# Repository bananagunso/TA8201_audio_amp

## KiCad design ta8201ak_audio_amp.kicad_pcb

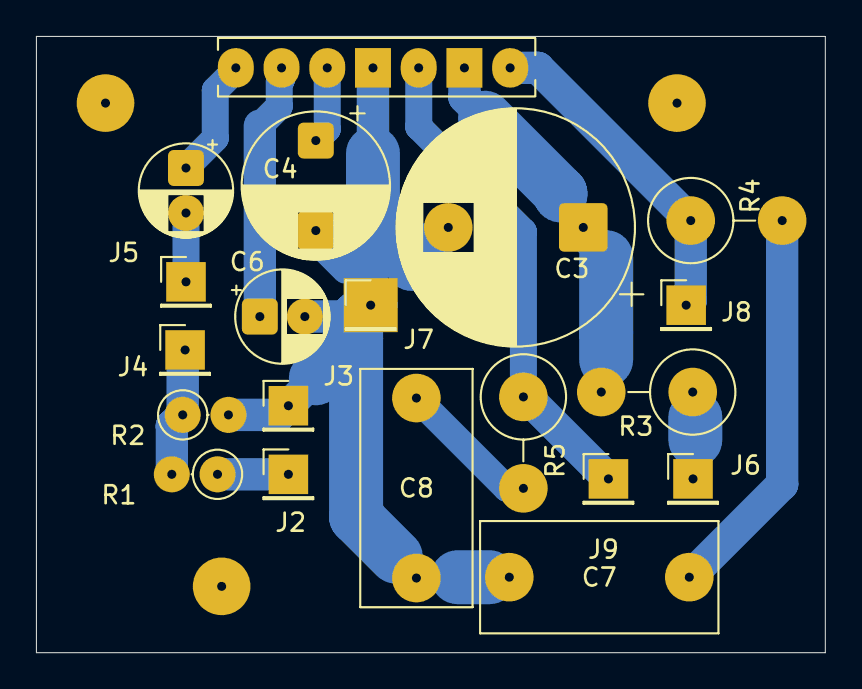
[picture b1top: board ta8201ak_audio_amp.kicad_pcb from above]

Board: 2 copper layers, 43.8 x 34.2 mm, 23 parts (0 on the bottom side), 13 nets.

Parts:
C3: 1000uF; CP_Radial_D13.0mm_P7.50mm
C4: 220u; CP_Radial_D8.0mm_P5.00mm
C5: 4.7u; CP_Radial_D5.0mm_P2.50mm
C6: 47u; CP_Radial_D5.0mm_P2.50mm
C7, C8: 0.15u; C_Rect_L13.0mm_W6.0mm_P10.00mm_FKS3_FKP3_MKS4
H1, H2, H3: MountingHole; MountingHole_3.2mm_M3
J2: IN; PinHeader_1x01_P2.54mm_Vertical
J3: GND; PinHeader_1x01_P2.54mm_Vertical
J4: RV1_3; PinHeader_1x01_P2.54mm_Vertical
J5: RV1_2; PinHeader_1x01_P2.54mm_Vertical
J6: Vcc; PinHeader_1x01_P2.54mm_Vertical
J7: Gnd; PinHeader_1x01_P2.54mm_Vertical
J8: Out1; PinHeader_1x01_P2.54mm_Vertical
J9: Out2; PinHeader_1x01_P2.54mm_Vertical
R1: 200k; R_Axial_DIN0207_L6.3mm_D2.5mm_P2.54mm_Vertical
R2: 820k; R_Axial_DIN0207_L6.3mm_D2.5mm_P2.54mm_Vertical
R3: 2.2Ω; R_Axial_DIN0414_L11.9mm_D4.5mm_P5.08mm_Vertical
R4, R5: 2.2; R_Axial_DIN0414_L11.9mm_D4.5mm_P5.08mm_Vertical
U1: TA8201AK

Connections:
GND: C3.2, C4.2, C6.2, C7.2, C8.2, J3.1, J7.1, R2.2, U1.4 (GND)
unnamed: C7.1, R4.2
unnamed: C8.1, R5.2
unnamed: J2.1, R1.1
unnamed: J4.1, R1.2, R2.1
unnamed: C5.2, J5.1
unnamed: J8.1, R4.1, U1.7 (OUT-1)
unnamed: J9.1, R5.1, U1.5 (OUT-2)
unnamed: C5.1, U1.1 (IN)
unnamed: C6.1, U1.2 (NF)
unnamed: C4.1, U1.3 (R.F)
unnamed: C3.1, R3.2, U1.6 (VCC)
VCC: J6.1, R3.1

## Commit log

2025-12-02 抵抗560Ωを追加Cを3.3uF,33uFに変更
2025-12-02 配置の修正
2025-12-03 配置変更、ジャンパを減らす。
2025-12-03 配置変更、アッテネーター追加、ベタ追加。
2025-12-08 電解コンデンサの足幅修正
2025-12-17 発振が酷いので部品配置を変更して解決できた 2.2Ω以外の抵抗は無くても利得が大きすぎるといったことは無いとおもう。
2026-01-27 発振が酷いので配置の見直しと配線を太くした
2026-01-28 ドリル穴が大きかったのを修正
2026-01-28 ドリル穴の修正
2026-03-03 配置と配線を修正
    配線の修正
2026-03-03 仕切り直す
2026-03-03 エレキギター向けに抵抗やコンデンサを変更
2026-03-04 利得制限の抵抗は外した アッテネーターの合成抵抗をエレキギター向けに1Mに近づけた 高音補正用のセラミックコンデンサとボリュームを追加
2026-03-04 GNDが細い一点で繋がっていたので少しでも太くなるよう配置修正
2026-03-05 ベタGNDをやめ、音声がICに入るまでのGNDと電源のGNDを分離した。
2026-03-06 パッド: 円形 Φ2.0 / 四角 2.0×2.0 / SIP 1.6×2.2 配線: 電源 2.0 / 信号 1.5 クリアランス: 0.5 ティアドロップ適用 ネジ穴をスルーホールにして真ん中が白抜きになるように 直角を排除
2026-03-06 ICのフットプリントを修正
2026-03-06 ブライトスイッチのコンデンサはスイッチ直付けにして配置変更
2026-03-12 パッドの大きさを修正
2026-03-12 配線の太さ、パッドの大きさを大きくした
2026-04-04 ハムノイズ対策に抵抗を追加してGNDの取り方を変更
